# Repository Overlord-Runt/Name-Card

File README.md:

# Name-Card

Hello!\
This is a name card I made for me to wear at hackathons and events.\
It has 6 leds, 6 Buttons, and a Buzzer, all powered on a CR2032 Cell Battery.

## What This does

This is a nametag that clips onto your shirt with a safety pin.\
It has 5 LEDs that turn on through buttons on the right and a buzzer that turns on through the button on the left.\
The 6th LED is to express my social battery as it depreciates throughout the day.\
All of this runs on a 3V CR2032 cell battery

## PCB

\

## Schematic

## How to Build

Go to any pcb maker and give them the production files.\
Order The parts and solder them onto the pcb\
Yay you did it.

OPTIONAL: You can edit the pcb files and personalise it a bit

## BOM

6 LEDs(Various colours)\
6 6mm Buttons\
7 220 Ohm Resistors\
1 CR2032 Battery Holder\
1 Poteniometer\
1 CR2032 Battery\
1 Buzzer\
1 PCB

Made By `@Taran The Idiot` from Hack Club

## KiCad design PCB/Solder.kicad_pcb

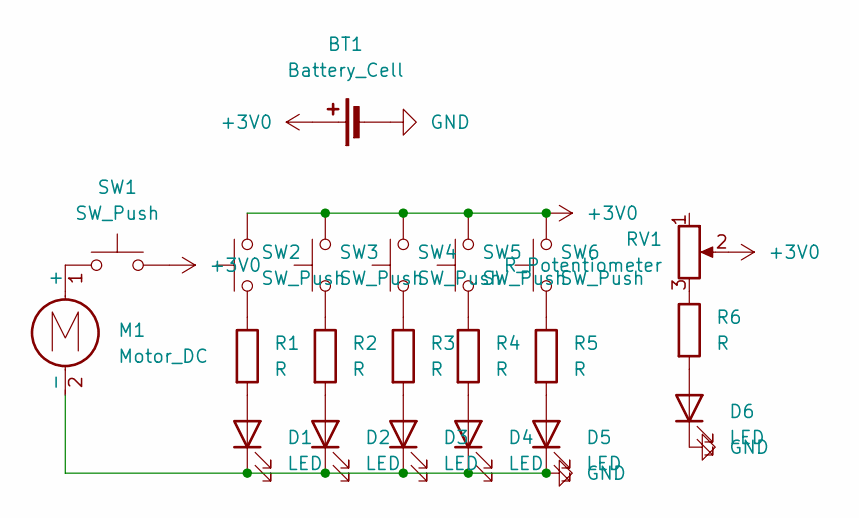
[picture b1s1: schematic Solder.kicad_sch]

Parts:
BT1: Battery_Cell; BatteryHolder_Keystone_3002_1x2032
D1, D2, D3, D4, D5, D6: LED; LED_D5.0mm
M1: Motor_DC; PinSocket_1x02_P2.54mm_Vertical
R1, R2, R3, R4, R5, R6: R; R_Axial_DIN0207_L6.3mm_D2.5mm_P7.62mm_Horizontal
RV1: R_Potentiometer; Potentiometer_Vishay_T73YP_Vertical
SW1, SW2, SW3, SW4, SW5, SW6: SW_Push; SW_PUSH_6mm

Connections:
+3V0: BT1.1 (+), RV1.2, SW1.2, SW2.2, SW3.2, SW4.2, SW5.2, SW6.2
GND: BT1.2 (-), D1.1 (K), D2.1 (K), D3.1 (K), D4.1 (K), D5.1 (K), D6.1 (K), M1.2 (-)
unnamed: D1.2 (A), R1.2
unnamed: D2.2 (A), R2.2
unnamed: D3.2 (A), R3.2
unnamed: D4.2 (A), R4.2
unnamed: D5.2 (A), R5.2
unnamed: D6.2 (A), R6.2
unnamed: M1.1 (+), SW1.1
unnamed: R1.1, SW2.1
unnamed: R2.1, SW3.1
unnamed: R3.1, SW4.1
unnamed: R4.1, SW5.1
unnamed: R5.1, SW6.1
unnamed: R6.1, RV1.3

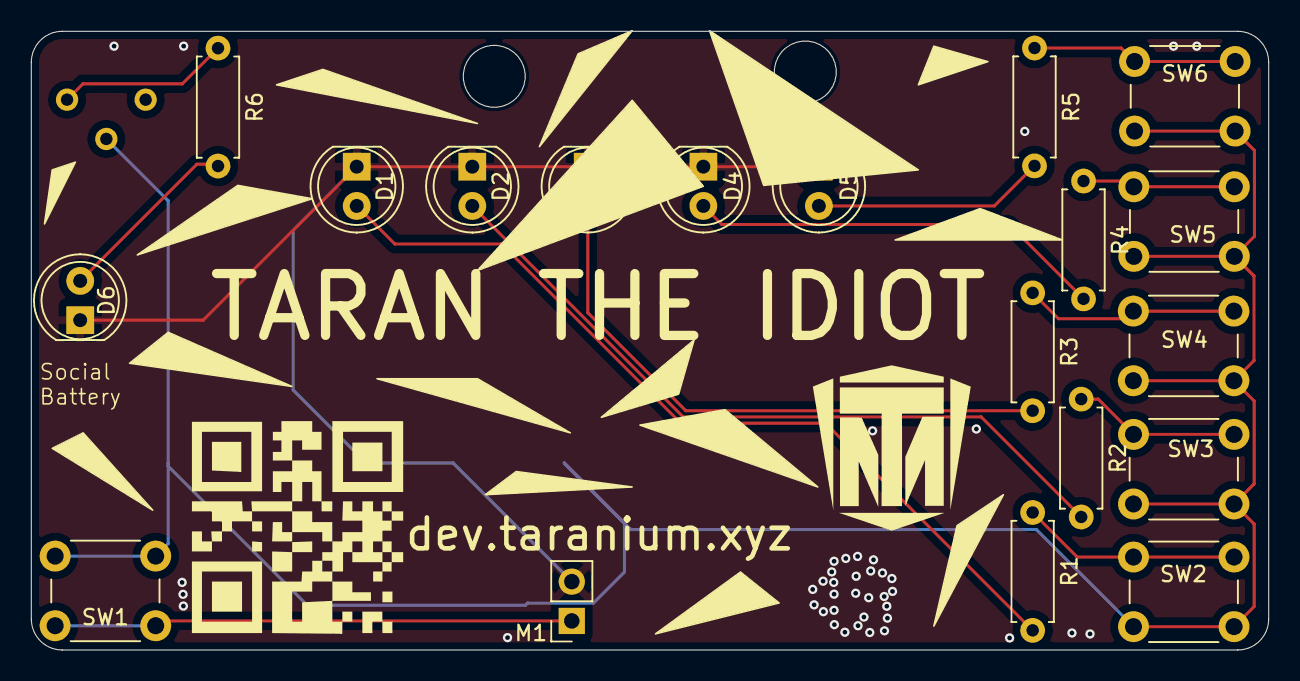
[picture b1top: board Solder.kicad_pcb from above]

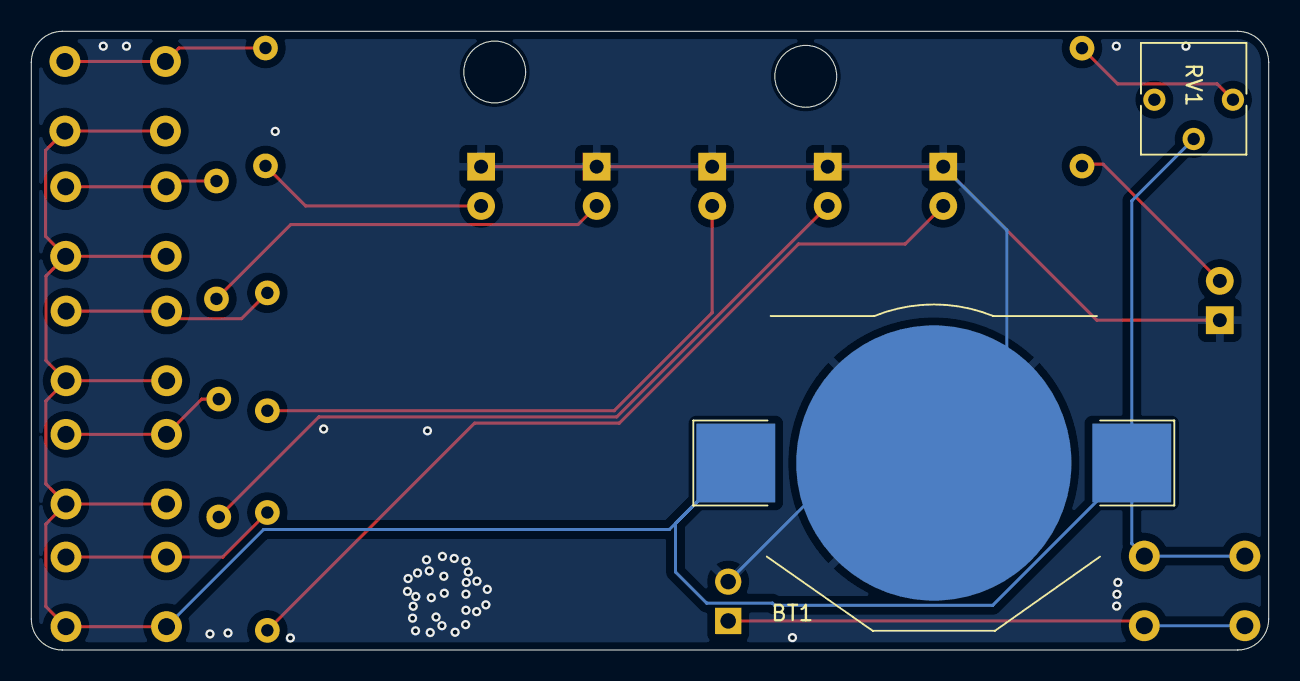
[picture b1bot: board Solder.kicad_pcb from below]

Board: 2 copper layers, 80.0 x 40.0 mm, 21 parts (2 on the bottom side), 15 nets.

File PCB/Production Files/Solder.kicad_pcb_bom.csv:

Designator,Quantity,Value,Footprint,Package,MPN,DNP,Mount_Type,Description,Sim.Pins
,1,,,,,,tht,,
BT1,1,Battery_Cell,BatteryHolder_Keystone_3002_1x2032,,,,smt,Single-cell battery,
"D1, D2, D3, D4, D5, D6",6,LED,LED_D5.0mm,,,,tht,Light emitting diode,1=K 2=A
M1,1,Motor_DC,PinSocket_1x02_P2.54mm_Vertical,,,,tht,DC Motor,
"R1, R2, R3, R4, R5, R6",6,R,R_Axial_DIN0207_L6.3mm_D2.5mm_P7.62mm_Horizontal,,,,tht,Resistor,
RV1,1,R_Potentiometer,Potentiometer_Vishay_T73YP_Vertical,,,,tht,Potentiometer,
"SW1, SW2, SW3, SW4, SW5, SW6",6,SW_Push,SW_PUSH_6mm,,,,tht,"Push button switch, generic, two pins",
